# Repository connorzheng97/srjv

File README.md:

# srjv
SR-JV80 Programmable Expansion Card with ESP32 Wi-Fi
- Product info page at https://www.ddzheng.cc/?page_id=666
- Blog post at https://www.ddzheng.cc/?p=617

This board is a re-writable ROM card with a Wi-Fi based user interface. It can store a ROM image up to 8MB/64Mbit, usually custom authored, and be used in compatible Roland synthesizers in place of an original SR-JV80 series expansion card to research the sound generation and synthesizing.

# Hardware Info
- ESP32-S3 Wroom module requires at least 2 MB Flash (No OTA) or 4 MB (with OTA).
- The NOR flash can be TSSOP 48 or 56 pin, 8 MB or more, 70ns or faster, with byte (8-bit) mode support. Regularly used for production is MX29LV640
- Connector is 40 pin SCSI all plastic connector or similar. The original card use MOLEX 52326-0401
- Reverse taped LED is only required for SMT production. For hand assembling regular 1206 LED can be used.

# Fabricating
4-layer board. Can also be made with 2 layers without modification. Assemble as indicated (DNP = do not populate) in schematic.

# Licsensing

Copyright Connor Zheng 2025.

This source describes Open Hardware and is licensed under the CERN-OHLW v2 or later. You may redistribute and modify this documentation and make products using it under the terms of the CERN-OHL-W v2 [https:/cern.ch/cern-ohl](https:/cern.ch/cern-ohl). This documentation is distributed WITHOUT ANY EXPRESS OR IMPLIED WARRANTY, INCLUDING OF MERCHANTABILITY, SATISFACTORY QUALITY AND FITNESS FOR A PARTICULAR PURPOSE. Please see the CERN-OHL-W v2 for applicable conditions.

Source location: [https://github.com/connorzheng97/srjv](https://github.com/connorzheng97/srjv)

As per CERN-OHL-W v2 section 4.1, should You produce hardware based on these sources, You must maintain the Source Location visible on the external case and PCB top layer silkscreen of the SRJV or other product you make using this documentation.

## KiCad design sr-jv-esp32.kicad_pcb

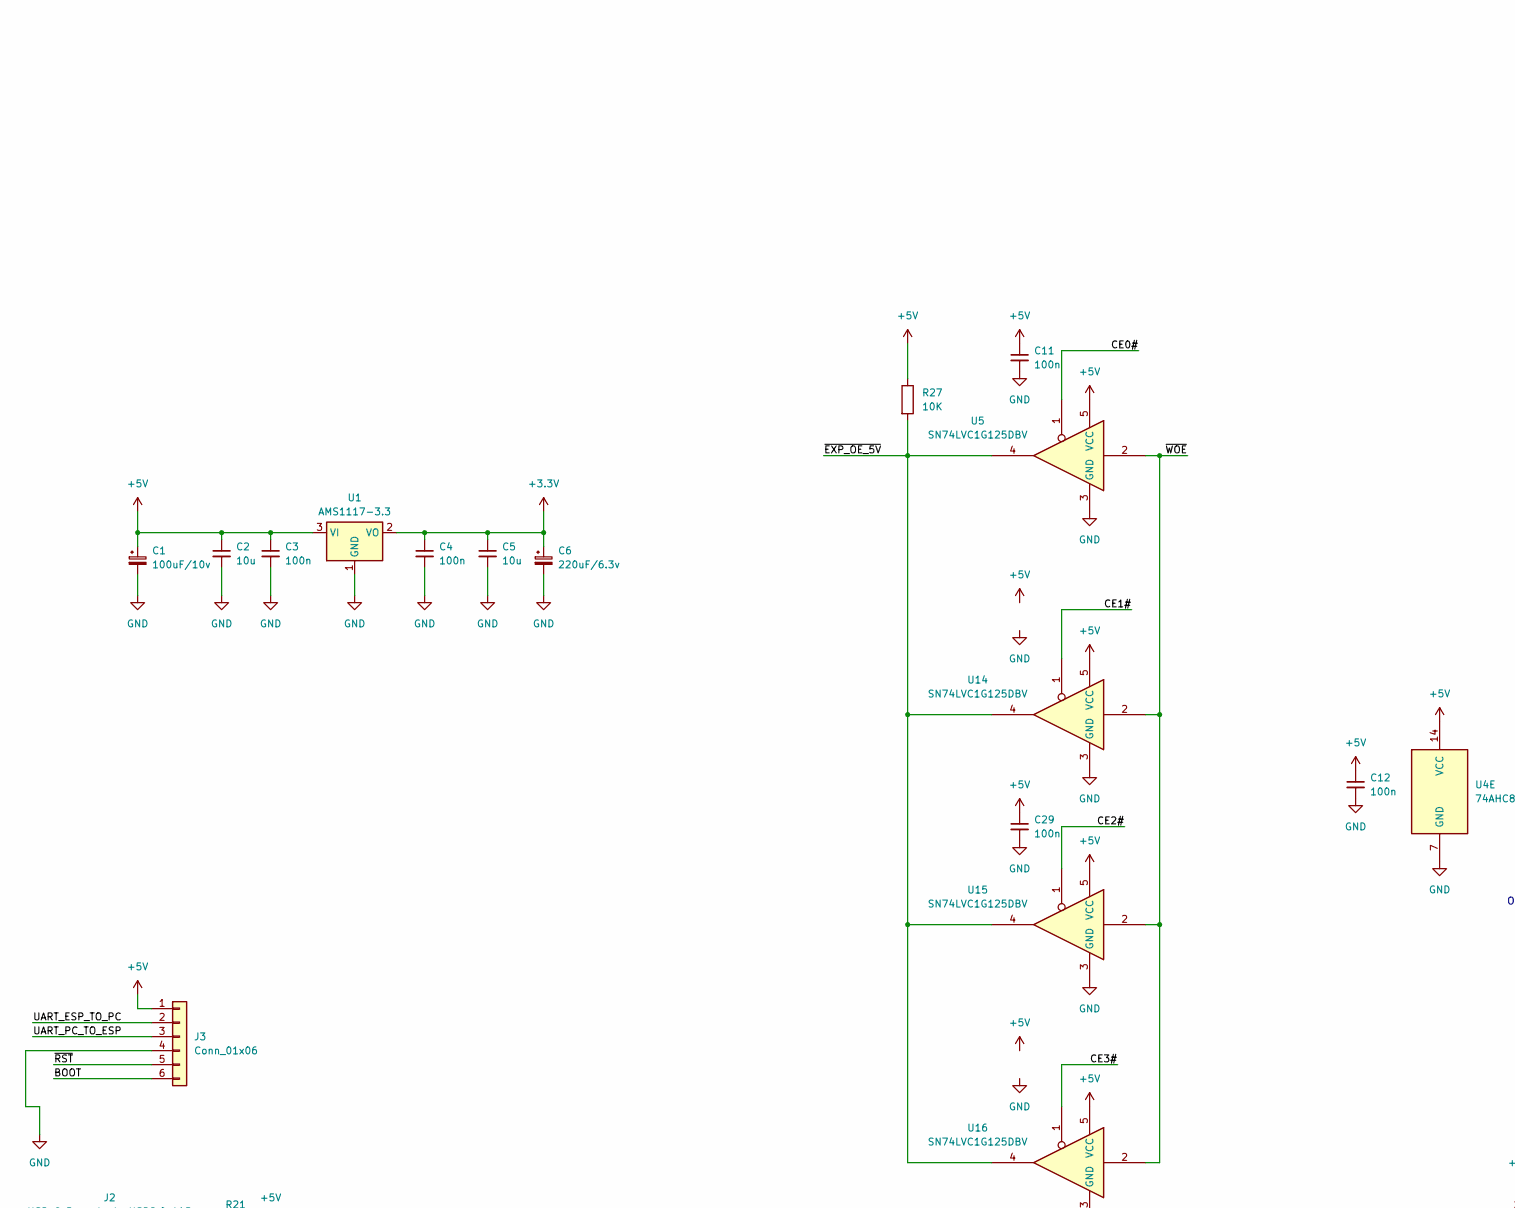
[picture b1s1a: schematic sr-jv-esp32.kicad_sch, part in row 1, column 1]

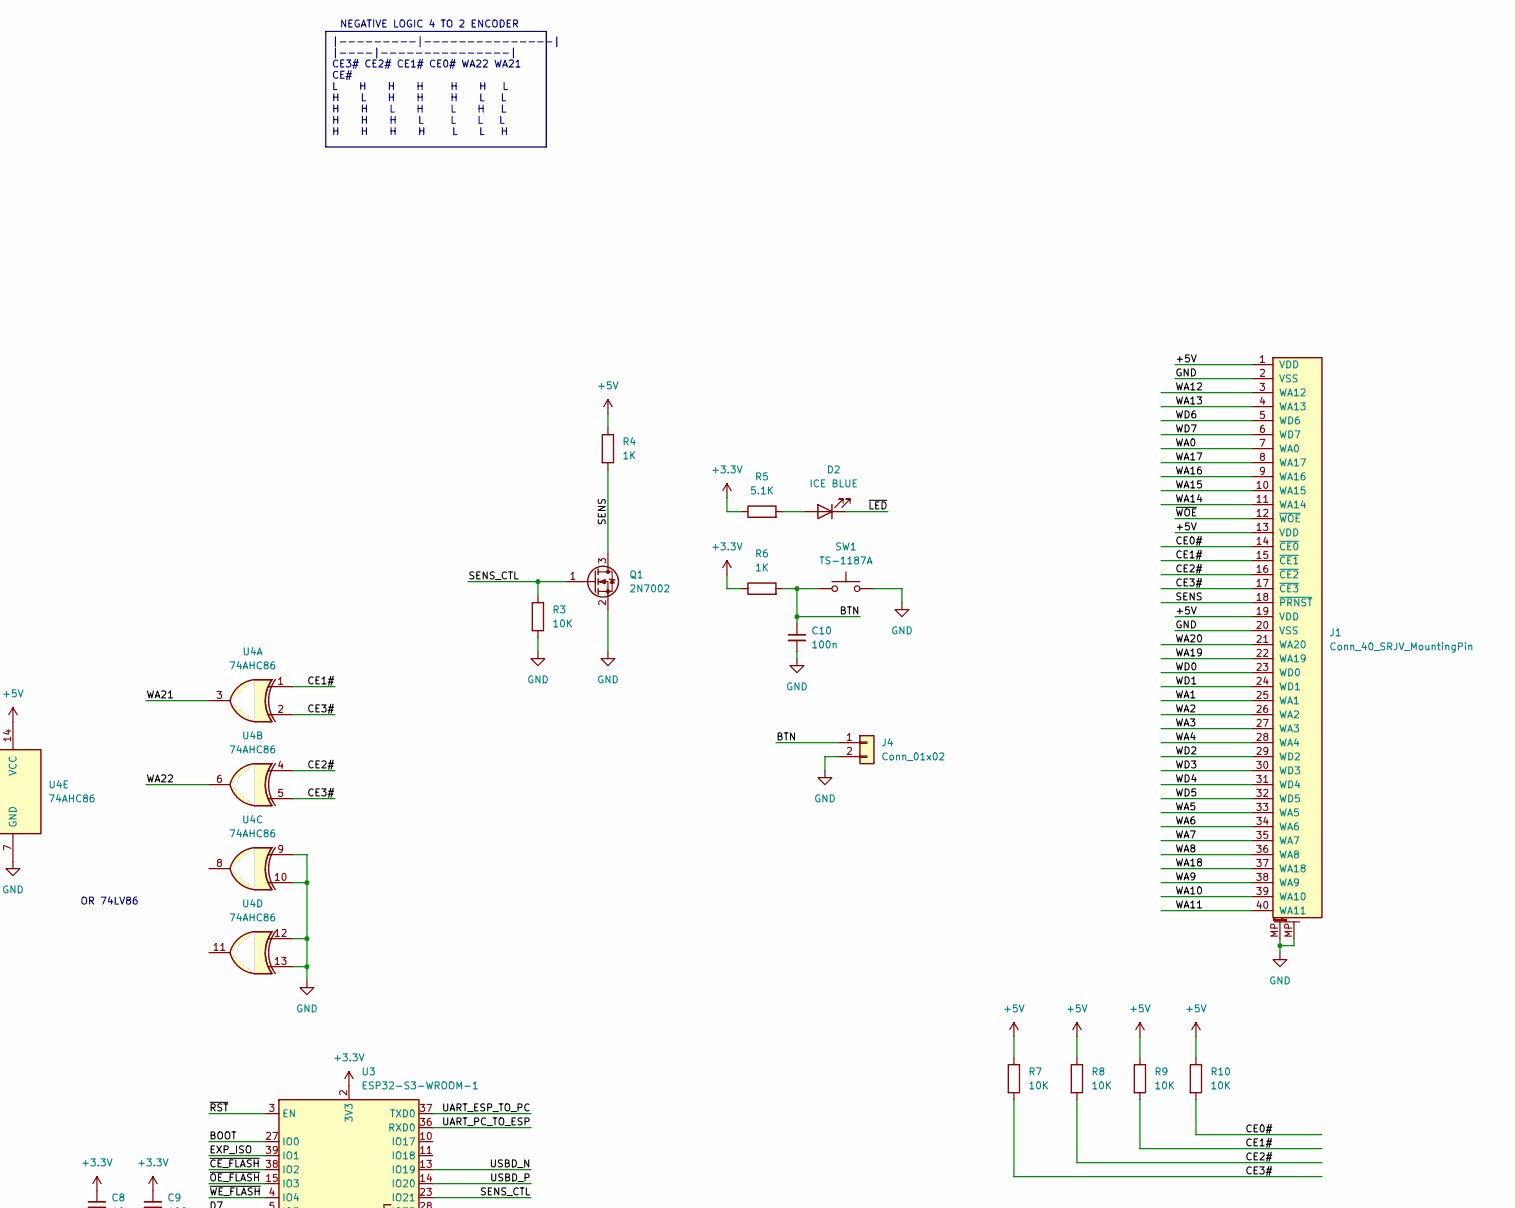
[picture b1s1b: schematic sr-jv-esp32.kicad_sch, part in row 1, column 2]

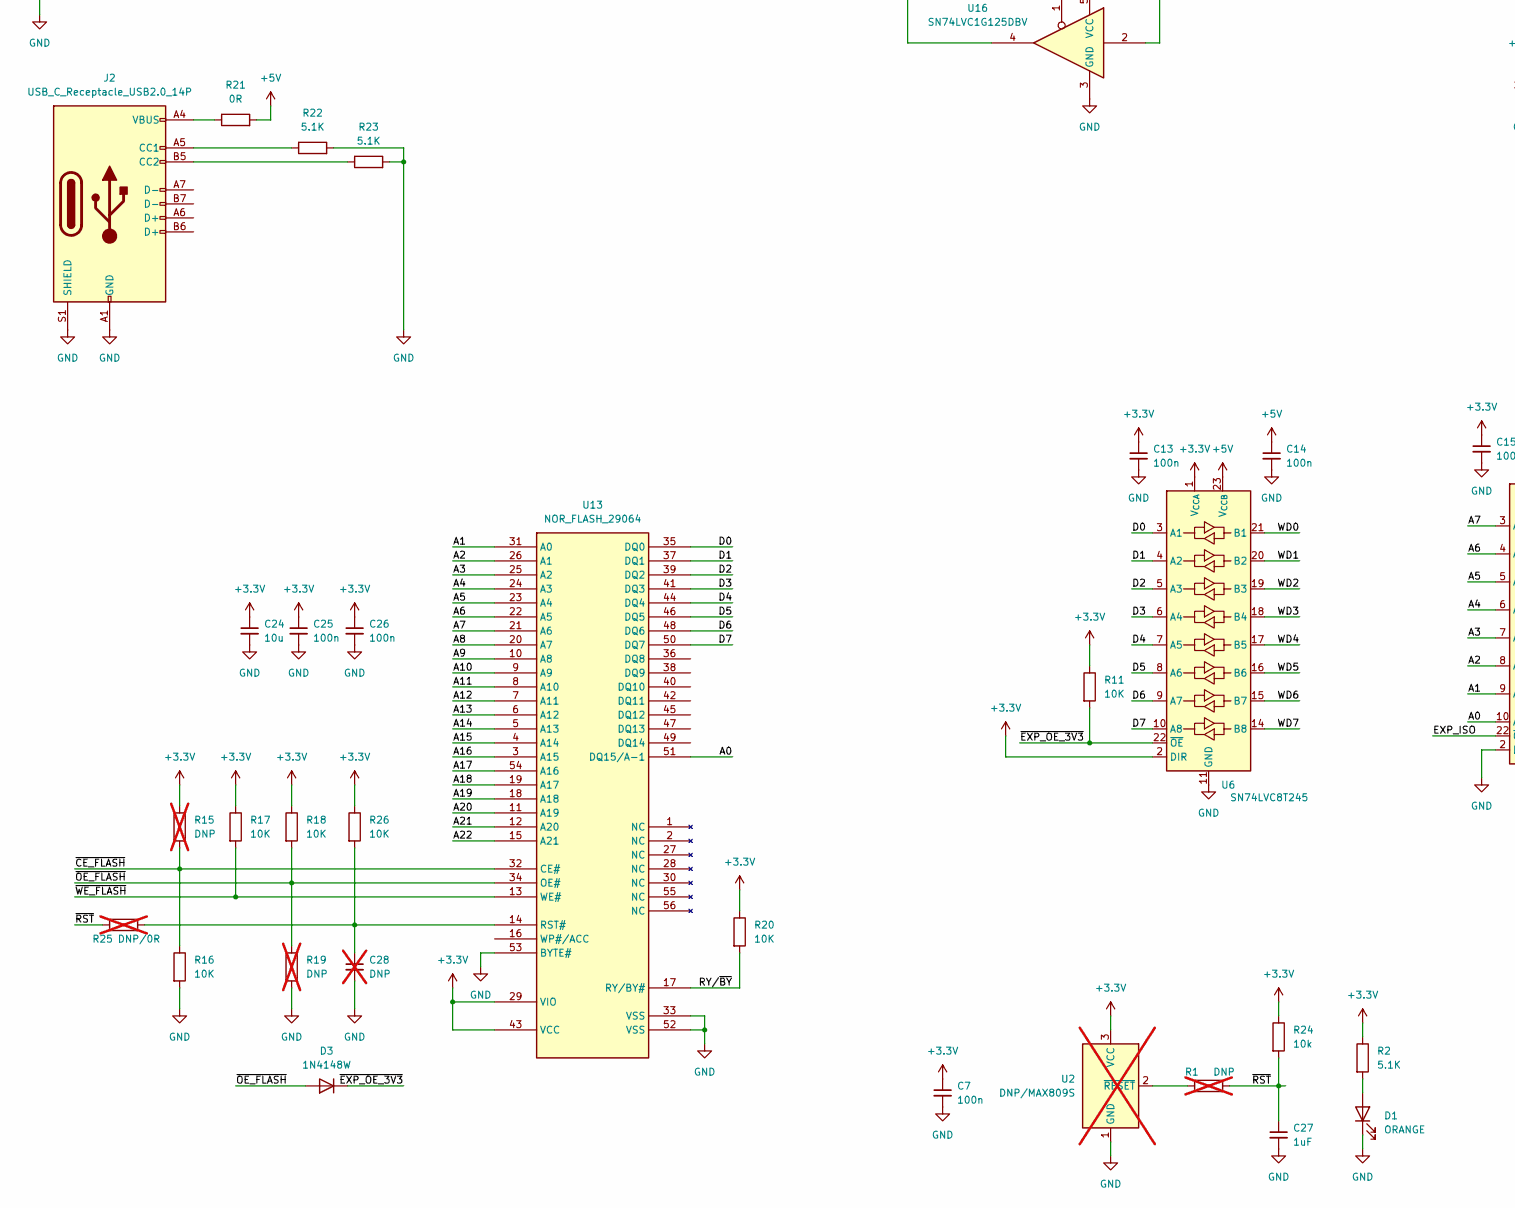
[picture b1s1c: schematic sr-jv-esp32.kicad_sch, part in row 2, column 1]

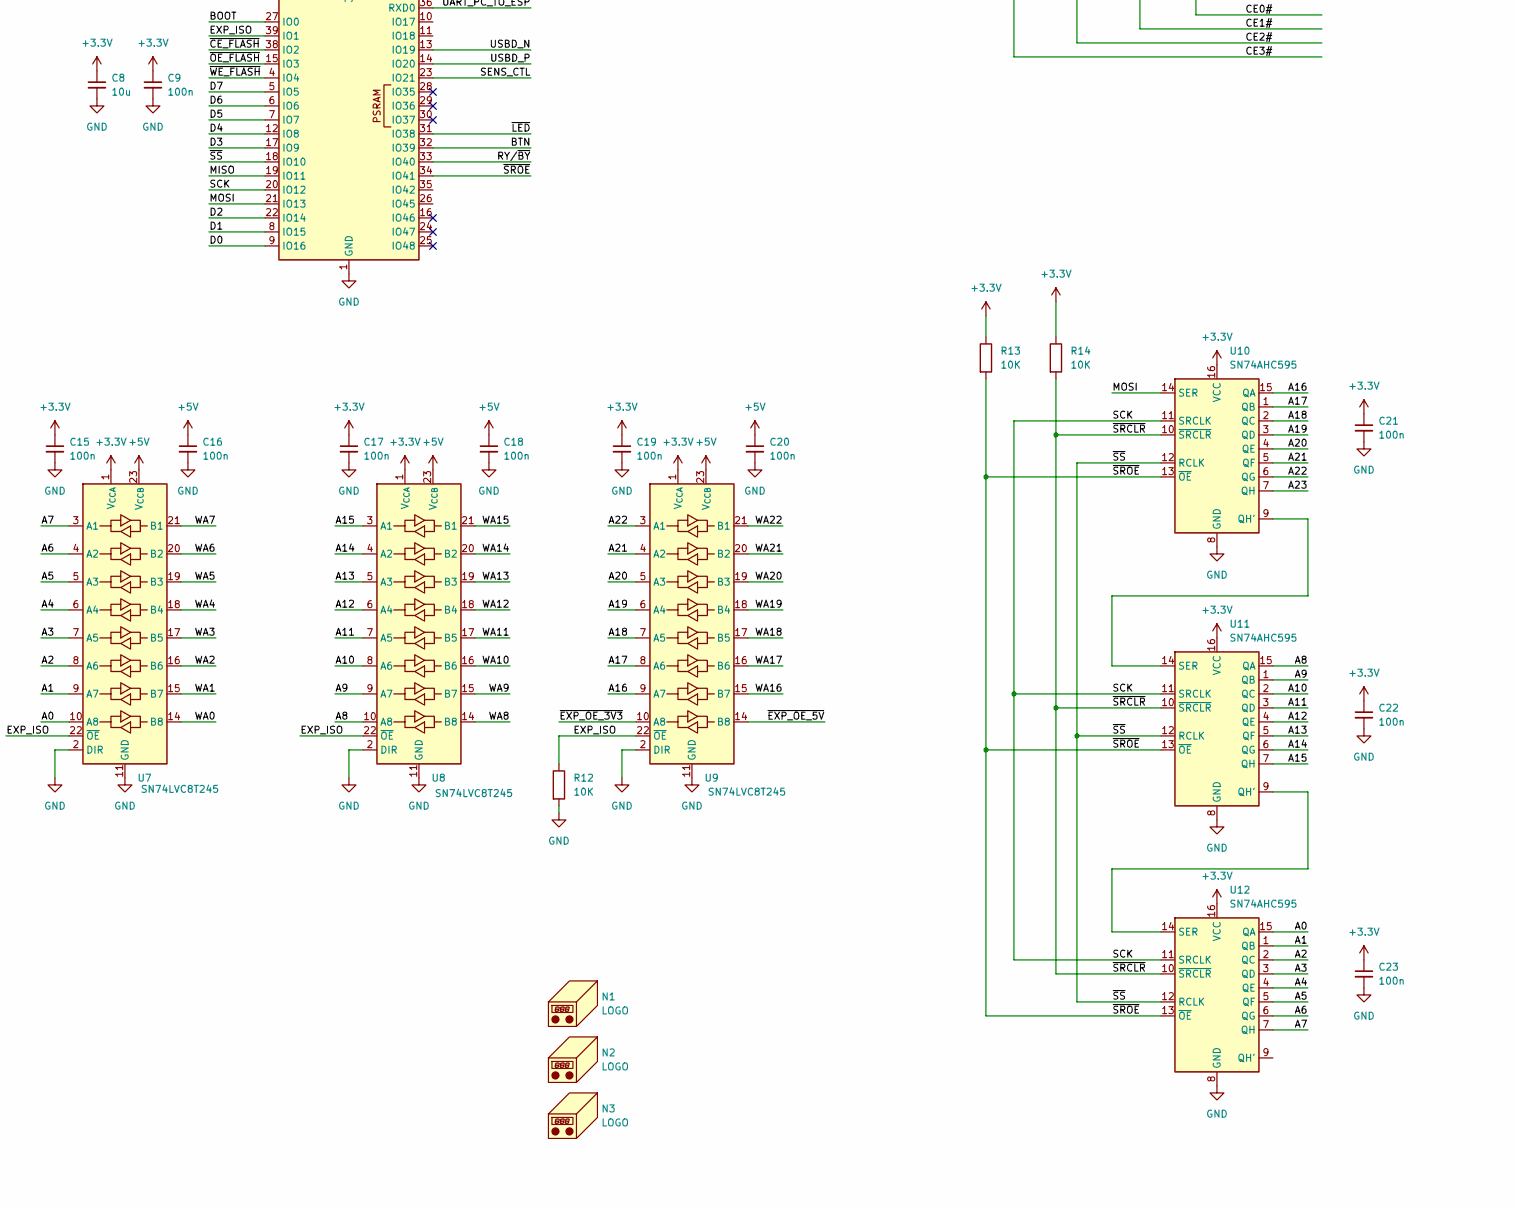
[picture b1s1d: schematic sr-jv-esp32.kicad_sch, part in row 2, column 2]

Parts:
C1: 100uF/10v; CP_Radial_D6.3mm_P2.50mm
C2, C5, C8, C24: 10u; C_0603_1608Metric
C3, C4, C7, C9, C10, C11, C12, C13, C14, C15, C16, C17, C18, C19, C20, C21, C22, C23, C25, C26, C29: 100n; C_0603_1608Metric
C6: 220uF/6.3v; CP_Radial_D6.3mm_P2.50mm
C27: 1uF; C_0603_1608Metric
C28: DNP; C_0603_1608Metric; not fitted
D1: ORANGE; LED_1206_3216Metric_ReverseMount
D2: ICE BLUE; LED_1206_3216Metric_ReverseMount
D3: 1N4148W; D_SOD-123
J1: Conn_40_SRJV_MountingPin; CONN_40P_SCSI_THT_Vertical
J2: USB_C_Receptacle_USB2.0_14P; USB_C_Receptacle_GCT_USB4105-xx-A_16P_TopMnt_Horizontal
J3: Conn_01x06; PinHeader_1x06_P2.54mm_Vertical
J4: Conn_01x02; JST_XH_B2B-XH-A_1x02_P2.50mm_Vertical
N1: LOGO; OSHW-Logo_5.7x6mm_SilkScreen
N2: LOGO; ESD-Logo_6.6x6mm_SilkScreen
N3: LOGO; WEEE-Logo_5.6x8mm_SilkScreen
Q1: 2N7002; SOT-23
R1, R15, R19: DNP; R_0603_1608Metric; not fitted
R2, R5, R22, R23: 5.1K; R_0603_1608Metric
R3, R7, R8, R9, R10, R11, R12, R13, R14, R16, R17, R18, R20, R26, R27: 10K; R_0603_1608Metric
R4, R6: 1K; R_0603_1608Metric
R21: 0R; R_0603_1608Metric
R24: 10k; R_0603_1608Metric
R25: DNP/0R; R_0603_1608Metric; not fitted
SW1: TS-1187A; SW_Push_1P1T_XKB_TS-1187A_LONGPAD
U1: AMS1117-3.3; SOT-223-3_TabPin2
U2: DNP/MAX809S; SOT-23; not fitted
U3: ESP32-S3-WROOM-1
U4: 74AHC86; TSSOP-14_4.4x5mm_P0.65mm
U5, U14, U15, U16: SN74LVC1G125DBV; SOT-23-5
U6, U7, U8, U9: SN74LVC8T245; TSSOP-24_4.4x7.8mm_P0.65mm
U10, U11, U12: SN74AHC595; TSSOP-16_4.4x5mm_P0.65mm
U13: NOR_FLASH_29064; TSOP-I-56_48_18.4x14mm_P0.5mm

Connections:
+3.3V: C4.1, C5.1, C6.1, C7.1, C8.1, C9.1, C13.1, C15.1, C17.1, C19.1, C21.1, C22.1, C23.1, C24.1, C25.1, C26.1, R2.1, R5.1, R6.1, R11.1, R13.1, R14.1, R15.1, R17.1, R18.1, R20.1, R24.1, R26.1, U1.2 (VO), U2.3 (VCC), U3.2 (3V3), U6.1 (V_{CCA}), U6.2 (DIR), U7.1 (V_{CCA}), U8.1 (V_{CCA}), U9.1 (V_{CCA}), U10.16 (VCC), U11.16 (VCC), U12.16 (VCC), U13.29 (VIO), U13.43 (VCC)
+5V: C1.1, C2.1, C3.1, C11.1, C12.1, C14.1, C16.1, C18.1, C20.1, C29.1, J1.1 (VDD), J1.13 (VDD), J1.19 (VDD), J3.1, R4.1, R7.1, R8.1, R9.1, R10.1, R21.2, R27.1, U1.3 (VI), U4.14 (VCC), U5.5 (VCC), U6.23 (V_{CCB}), U6.24 (V_{CCB}), U7.23 (V_{CCB}), U7.24 (V_{CCB}), U8.23 (V_{CCB}), U8.24 (V_{CCB}), U9.23 (V_{CCB}), U9.24 (V_{CCB}), U14.5 (VCC), U15.5 (VCC), U16.5 (VCC)
/A0: U7.10 (A8), U12.15 (QA), U13.51 (DQ15/A-1)
/A1: U7.9 (A7), U12.1 (QB), U13.31 (A0)
/A2: U7.8 (A6), U12.2 (QC), U13.26 (A1)
/A3: U7.7 (A5), U12.3 (QD), U13.25 (A2)
/A4: U7.6 (A4), U12.4 (QE), U13.24 (A3)
/A5: U7.5 (A3), U12.5 (QF), U13.23 (A4)
/A6: U7.4 (A2), U12.6 (QG), U13.22 (A5)
/A7: U7.3 (A1), U12.7 (QH), U13.21 (A6)
/A8: U8.10 (A8), U11.15 (QA), U13.20 (A7)
/A9: U8.9 (A7), U11.1 (QB), U13.10 (A8)
/A10: U8.8 (A6), U11.2 (QC), U13.9 (A9)
/A11: U8.7 (A5), U11.3 (QD), U13.8 (A10)
/A12: U8.6 (A4), U11.4 (QE), U13.7 (A11)
/A13: U8.5 (A3), U11.5 (QF), U13.6 (A12)
/A14: U8.4 (A2), U11.6 (QG), U13.5 (A13)
/A15: U8.3 (A1), U11.7 (QH), U13.4 (A14)
/A16: U9.9 (A7), U10.15 (QA), U13.3 (A15)
/A17: U9.8 (A6), U10.1 (QB), U13.54 (A16)
/A18: U9.7 (A5), U10.2 (QC), U13.19 (A17)
/A19: U9.6 (A4), U10.3 (QD), U13.18 (A18)
/A20: U9.5 (A3), U10.4 (QE), U13.11 (A19)
/A21: U9.4 (A2), U10.5 (QF), U13.12 (A20)
/A22: U9.3 (A1), U10.6 (QG), U13.15 (A21)
/A23: U10.7 (QH)
/BOOT: J3.6, U3.27 (IO0)
/BTN: C10.1, J4.1, R6.2, SW1.1, U3.32 (IO39)
/CE0#: J1.14 (~CE0), R10.2, U5.1
/CE1#: J1.15 (~CE1), R9.2, U4.1, U14.1
/CE2#: J1.16 (~CE2), R8.2, U4.4, U15.1
/CE3#: J1.17 (~CE3), R7.2, U4.2, U4.5, U16.1
/D0: U3.9 (IO16), U6.3 (A1), U13.35 (DQ0)
/D1: U3.8 (IO15), U6.4 (A2), U13.37 (DQ1)
/D2: U3.22 (IO14), U6.5 (A3), U13.39 (DQ2)
/D3: U3.17 (IO9), U6.6 (A4), U13.41 (DQ3)
/D4: U3.12 (IO8), U6.7 (A5), U13.44 (DQ4)
/D5: U3.7 (IO7), U6.8 (A6), U13.46 (DQ5)
/D6: U3.6 (IO6), U6.9 (A7), U13.48 (DQ6)
/D7: U3.5 (IO5), U6.10 (A8), U13.50 (DQ7)
/EXP_ISO: R12.1, U3.39 (IO1), U7.22 (~OE), U8.22 (~OE), U9.22 (~OE)
/MISO: U3.19 (IO11)
/MOSI: U3.21 (IO13), U10.14 (SER)
/RY/~BY: R20.2, U3.33 (IO40), U13.17 (RY/BY#)
/SCK: U3.20 (IO12), U10.11 (SRCLK), U11.11 (SRCLK), U12.11 (SRCLK)
/SENS: J1.18 (~PRNST), Q1.3 (D), R4.2
/SENS_CTL: Q1.1 (G), R3.1, U3.23 (IO21)
/UART_ESP_TO_PC: J3.2, U3.37 (TXD0)
/UART_PC_TO_ESP: J3.3, U3.36 (RXD0)
/USBD_N: U3.13 (IO19)
/USBD_P: U3.14 (IO20)
/WA0: J1.7 (WA0), U7.14 (B8)
/WA1: J1.25 (WA1), U7.15 (B7)
/WA2: J1.26 (WA2), U7.16 (B6)
/WA3: J1.27 (WA3), U7.17 (B5)
/WA4: J1.28 (WA4), U7.18 (B4)
/WA5: J1.33 (WA5), U7.19 (B3)
/WA6: J1.34 (WA6), U7.20 (B2)
/WA7: J1.35 (WA7), U7.21 (B1)
/WA8: J1.36 (WA8), U8.14 (B8)
/WA9: J1.38 (WA9), U8.15 (B7)
/WA10: J1.39 (WA10), U8.16 (B6)
/WA11: J1.40 (WA11), U8.17 (B5)
/WA12: J1.3 (WA12), U8.18 (B4)
/WA13: J1.4 (WA13), U8.19 (B3)
/WA14: J1.11 (WA14), U8.20 (B2)
/WA15: J1.10 (WA15), U8.21 (B1)
/WA16: J1.9 (WA16), U9.15 (B7)
/WA17: J1.8 (WA17), U9.16 (B6)
/WA18: J1.37 (WA18), U9.17 (B5)
/WA19: J1.22 (WA19), U9.18 (B4)
/WA20: J1.21 (WA20), U9.19 (B3)
/WA21: U4.3, U9.20 (B2)
/WA22: U4.6, U9.21 (B1)
/WD0: J1.23 (WD0), U6.21 (B1)
/WD1: J1.24 (WD1), U6.20 (B2)
/WD2: J1.29 (WD2), U6.19 (B3)
/WD3: J1.30 (WD3), U6.18 (B4)
/WD4: J1.31 (WD4), U6.17 (B5)
/WD5: J1.32 (WD5), U6.16 (B6)
/WD6: J1.5 (WD6), U6.15 (B7)
/WD7: J1.6 (WD7), U6.14 (B8)
/~CE_FLASH: R15.2, R16.1, U3.38 (IO2), U13.32 (CE#)
/~EXP_OE_3V3: D3.1 (K), R11.2, U6.22 (~OE), U9.10 (A8)
/~EXP_OE_5V: R27.2, U5.4, U9.14 (B8), U14.4, U15.4, U16.4
/~LED: D2.1 (K), U3.31 (IO38)
/~OE_FLASH: D3.2 (A), R18.2, R19.1, U3.15 (IO3), U13.34 (OE#)
/~RST: C27.1, J3.5, R1.2, R24.2, R25.1, U3.3 (EN)
/~SRCLR: R14.2, U10.10 (~SRCLR), U11.10 (~SRCLR), U12.10 (~SRCLR)
/~SROE: R13.2, U3.34 (IO41), U10.13 (~OE), U11.13 (~OE), U12.13 (~OE)
/~SS: U3.18 (IO10), U10.12 (RCLK), U11.12 (RCLK), U12.12 (RCLK)
/~WE_FLASH: R17.2, U3.4 (IO4), U13.13 (WE#)
/~WOE: J1.12 (~WOE), U5.2, U14.2, U15.2, U16.2
GND: C1.2, C2.2, C3.2, C4.2, C5.2, C6.2, C7.2, C8.2, C9.2, C10.2, C11.2, C12.2, C13.2, C14.2, C15.2, C16.2, C17.2, C18.2, C19.2, C20.2, C21.2, C22.2, C23.2, C24.2, C25.2, C26.2, C27.2, C28.2, C29.2, D1.1 (K), J1.2 (VSS), J1.20 (VSS), J1.MP, J2.A1 (GND), J2.A12 (GND), J2.B1 (GND), J2.B12 (GND), J2.S1 (SHIELD), J3.4, J4.2, Q1.2 (S), R3.2, R12.2, R16.2, R19.2, R22.2, R23.2, SW1.2, U1.1 (GND), U2.1 (GND), U3.1 (GND), U3.40 (GND), U3.41 (GND), U4.7 (GND), U4.9, U4.10, U4.12, U4.13, U5.3 (GND), U6.11 (GND), U6.12 (GND), U6.13 (GND), U7.2 (DIR), U7.11 (GND), U7.12 (GND), U7.13 (GND), U8.2 (DIR), U8.11 (GND), U8.12 (GND), U8.13 (GND), U9.2 (DIR), U9.11 (GND), U9.12 (GND), U9.13 (GND), U10.8 (GND), U11.8 (GND), U12.8 (GND), U13.33 (VSS), U13.52 (VSS), U13.53 (BYTE#), U14.3 (GND), U15.3 (GND), U16.3 (GND)
unnamed: D1.2 (A), R2.2
unnamed: D2.2 (A), R5.2
unnamed: J2.A5 (CC1), R22.1
unnamed: J2.B5 (CC2), R23.1
unnamed: J2.A4 (VBUS), J2.A9 (VBUS), J2.B4 (VBUS), J2.B9 (VBUS), R21.1
unnamed: R1.1, U2.2 (~RESET)
unnamed: U10.9 (QH'), U11.14 (SER)
unnamed: U11.9 (QH'), U12.14 (SER)
unnamed: C28.1, R25.2, R26.2, U13.14 (RST#)

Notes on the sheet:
|---------|---------------| |----|---------------| CE3# CE2# CE1# CE0# WA22 WA21 CE# L H H H H H L H L H H H L L H H L H L H L H H H L L L L H H H H L L H
NEGATIVE LOGIC 4 TO 2 ENCODER
OR 74LV86

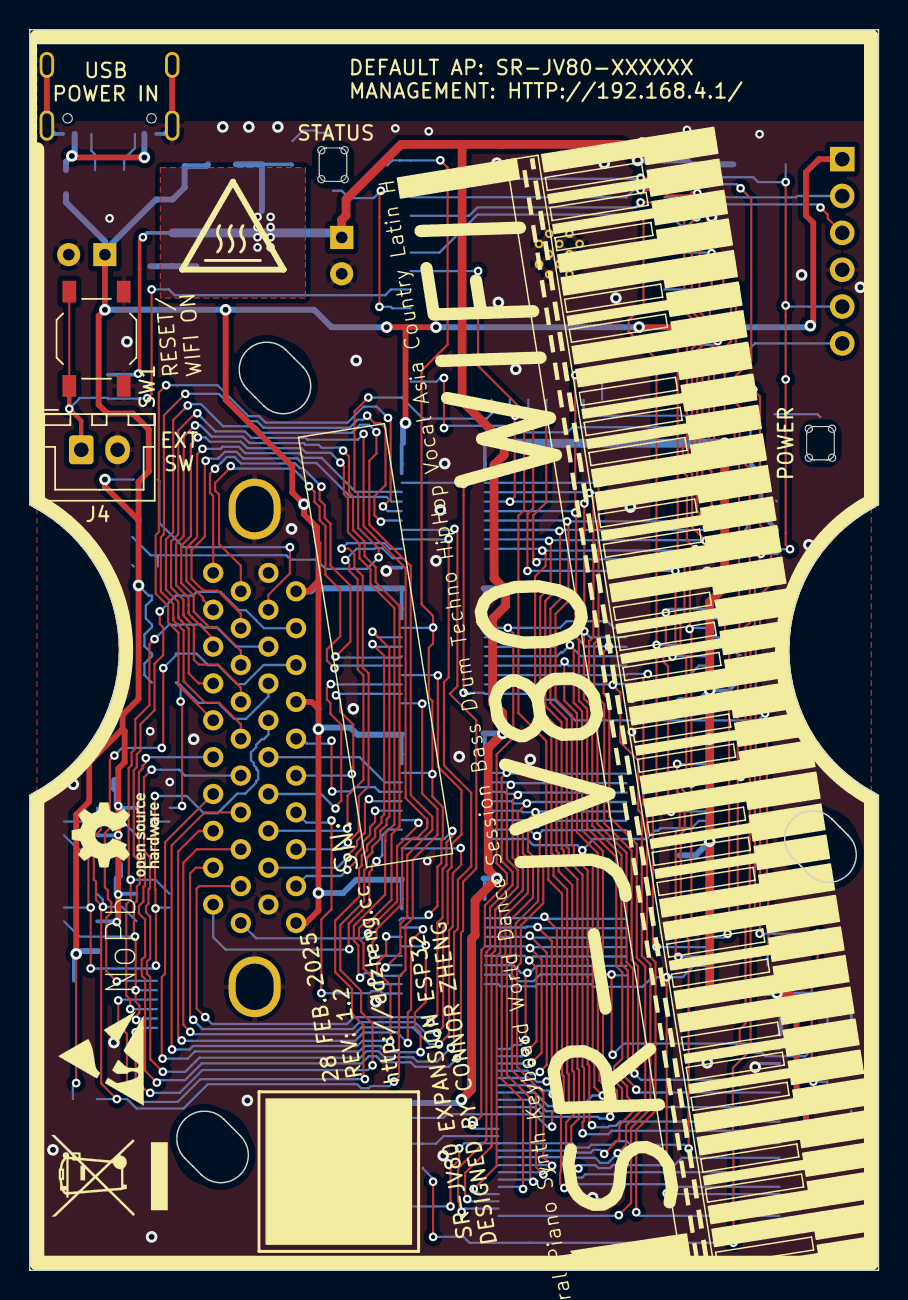
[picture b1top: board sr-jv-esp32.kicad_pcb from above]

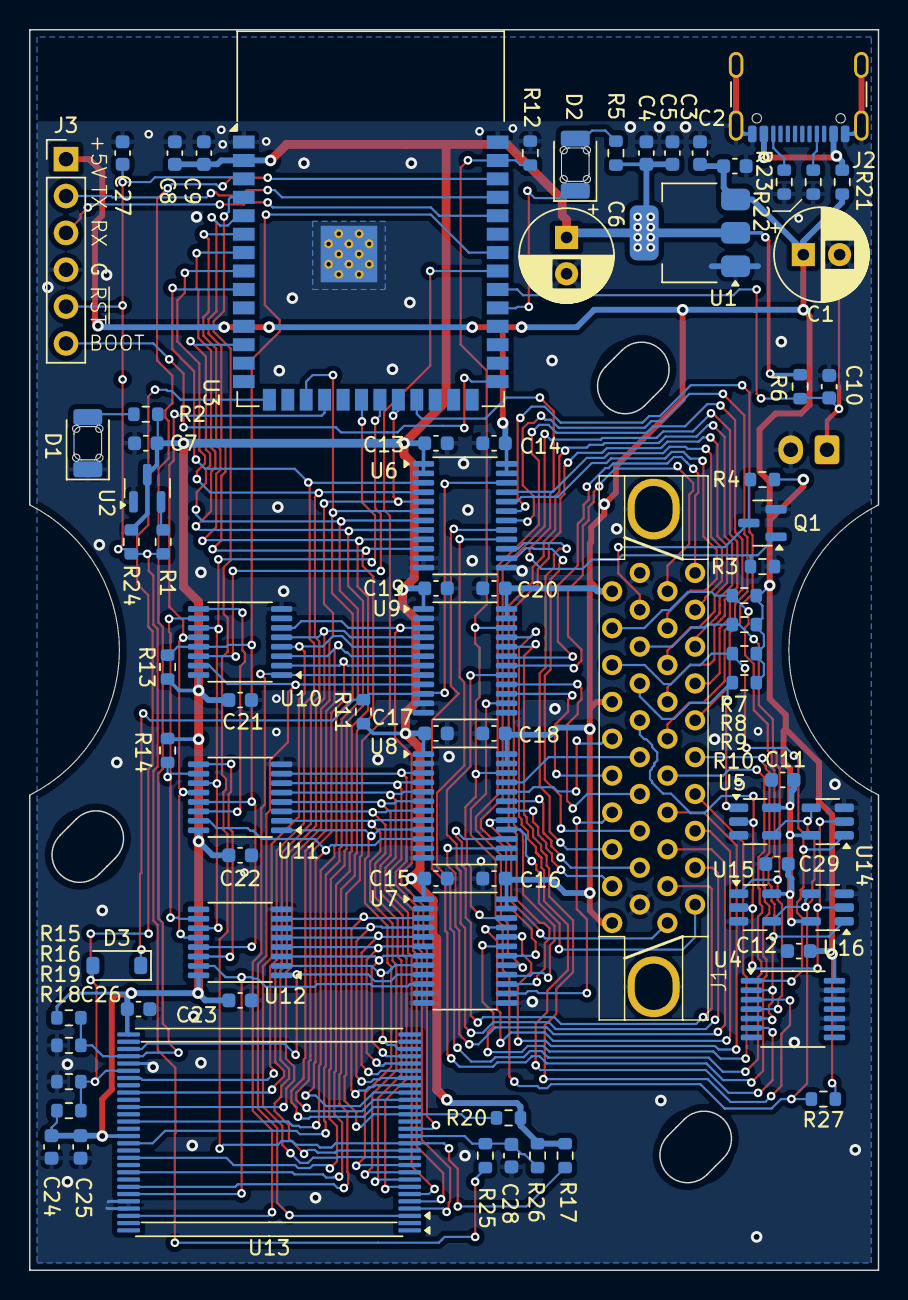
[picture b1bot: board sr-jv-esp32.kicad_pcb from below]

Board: 4 copper layers, 58.5 x 85.5 mm, 84 parts (79 on the bottom side), 99 nets.

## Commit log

2025-02-25 Initial commit HW Rev 1.1
2025-04-13 Upload MP 1.2 version
